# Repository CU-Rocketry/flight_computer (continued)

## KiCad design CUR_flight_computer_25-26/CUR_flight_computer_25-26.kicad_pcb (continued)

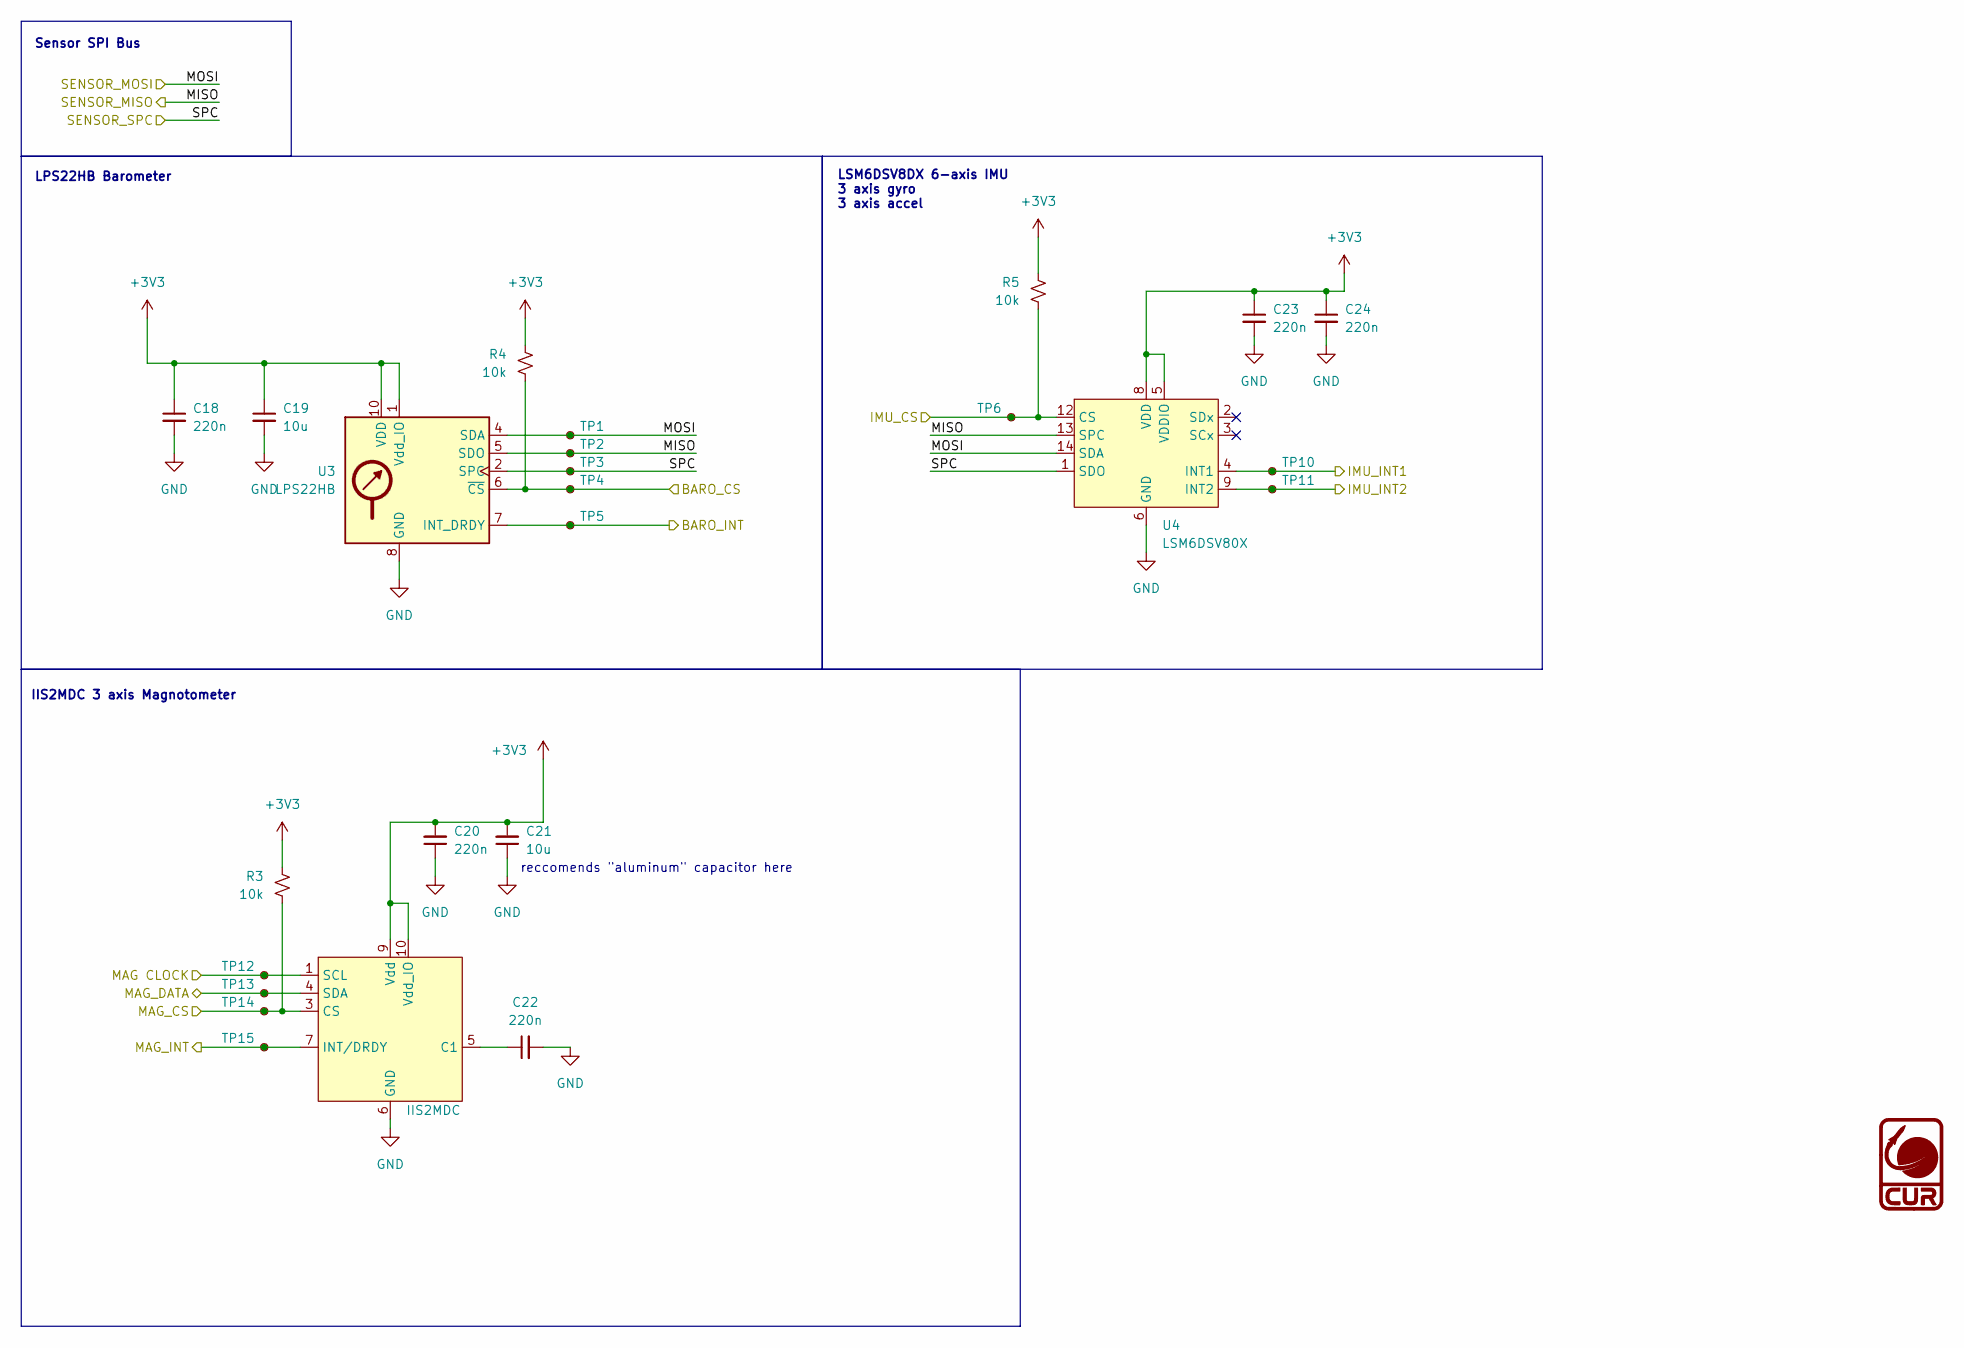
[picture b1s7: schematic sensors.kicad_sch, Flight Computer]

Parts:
C18, C20, C22, C23, C24: 220n; C_0603_1608Metric; MPN 0603B224K250CT
C19, C21: 10u; C_0603_1608Metric; MPN LMK107BBJ106MALT
R3, R4, R5: 10k; R_0603_1608Metric; MPN RC0603FR-0710KL
TP1, TP2, TP3, TP4, TP5, TP6, TP10, TP11, TP12, TP13, TP14, TP15: RCUCTE; TestPoint_Chip_RCUCTE_0603; MPN RCUCTE
U2: IIS2MDC; LGA-12_2X2X0P7_STM; MPN IIS2MDCTR
U3: LPS22HB; ST_HLGA-10_2x2mm_P0.5mm_LayoutBorder3x2y; MPN LPS22HHTR
U4: LSM6DSV80X; LGA-14_3x2.5mm_P0.5mm_LayoutBorder3x4y; MPN LSM6DSV80XTR

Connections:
+3V3: C18.1, C19.1, C20.2, C21.2, C23.1, C24.1, R3.1, R4.1, R5.1, U2.9 (Vdd), U2.10 (Vdd_IO), U3.1 (Vdd_IO), U3.10 (VDD), U4.5 (VDDIO), U4.8 (VDD); also elsewhere on the board
/MCU/BARO_CS: R4.2, TP4.1, U3.6 (~CS); also elsewhere on the board
/MCU/BARO_INT: TP5.1, U3.7 (INT_DRDY); also elsewhere on the board
/MCU/IMU_CS: R5.2, TP6.1, U4.12 (CS); also elsewhere on the board
/MCU/IMU_INT1: TP10.1, U4.4 (INT1); also elsewhere on the board
/MCU/IMU_INT2: TP11.1, U4.9 (INT2); also elsewhere on the board
/MCU/MAG CLOCK: TP12.1, U2.1 (SCL); also elsewhere on the board
/MCU/MAG_CS: R3.2, TP14.1, U2.3 (CS); also elsewhere on the board
/MCU/MAG_DATA: TP13.1, U2.4 (SDA); also elsewhere on the board
/MCU/MAG_INT: TP15.1, U2.7 (INT/DRDY); also elsewhere on the board
/Sensors/MISO: TP2.1, U3.5 (SDO), U4.13 (SPC); also elsewhere on the board
/Sensors/MOSI: TP1.1, U3.4 (SDA), U4.14 (SDA); also elsewhere on the board
/Sensors/SPC: TP3.1, U3.2 (SPC), U4.1 (SDO); also elsewhere on the board
GND: C18.2, C19.2, C20.1, C21.1, C22.2, C23.2, C24.2, U2.6 (GND), U2.8 (GND), U3.3 (GND), U3.8 (GND), U3.9 (GND), U4.6 (GND), U4.7 (GND); also elsewhere on the board
unnamed: C22.1, U2.5 (C1)

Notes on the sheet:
LSM6DSV8DX 6-axis IMU 3 axis gyro 3 axis accel
IIS2MDC 3 axis Magnotometer
reccomends "aluminum" capacitor here
Sensor SPI Bus
LPS22HB Barometer

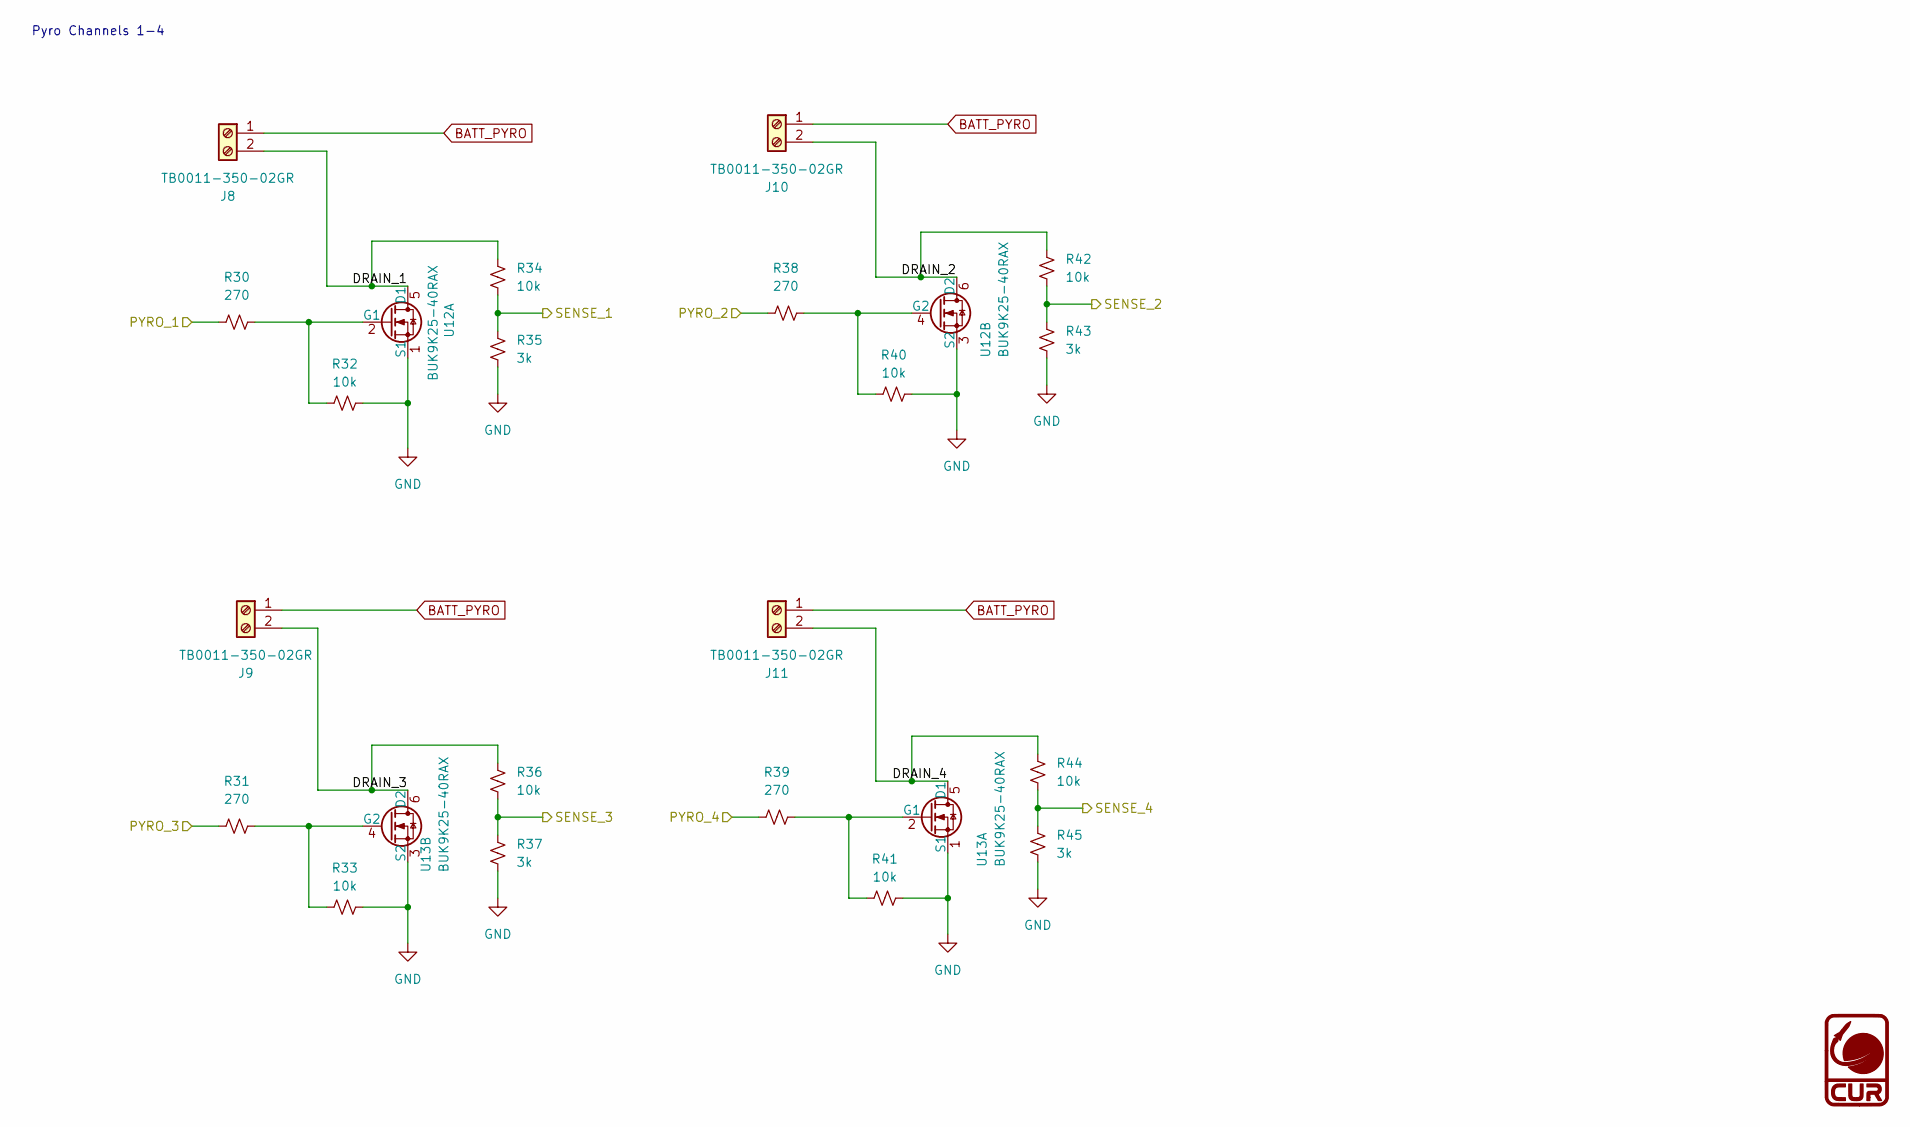
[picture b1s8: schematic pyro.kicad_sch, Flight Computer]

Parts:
J8, J9, J10, J11: TB0011-350-02GR; SAMESKY_TB0011-350-02GR; MPN TB0011-350-02GR
R30, R31, R38, R39: 270; R_0603_1608Metric; MPN RC0603JR-07270RL
R32, R33, R34, R36, R40, R41, R42, R44: 10k; R_0603_1608Metric; MPN RC0603FR-0710KL
R35, R37, R43, R45: 3k; R_0603_1608Metric; MPN RC0603FR-073KL
U12, U13: BUK9K25-40RAX; BUK9K2540RAX; MPN BUK9K25-40RAX

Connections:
/MCU/PYRO_1: R30.1; also elsewhere on the board
/MCU/PYRO_2: R38.1; also elsewhere on the board
/MCU/PYRO_3: R31.1; also elsewhere on the board
/MCU/PYRO_4: R39.1; also elsewhere on the board
/MCU/SENSE_1: R34.2, R35.1; also elsewhere on the board
/MCU/SENSE_2: R42.2, R43.1; also elsewhere on the board
/MCU/SENSE_3: R36.2, R37.1; also elsewhere on the board
/MCU/SENSE_4: R44.2, R45.1; also elsewhere on the board
/Pyro/DRAIN_1: J8.2, R34.1, U12.5 (D1)
/Pyro/DRAIN_2: J10.2, R42.1, U12.6 (D2)
/Pyro/DRAIN_3: J9.2, R36.1, U13.6 (D2)
/Pyro/DRAIN_4: J11.2, R44.1, U13.5 (D1)
BATT_PYRO: J8.1, J9.1, J10.1, J11.1; also elsewhere on the board
GND: R32.2, R33.2, R35.2, R37.2, R40.2, R41.2, R43.2, R45.2, U12.1 (S1), U12.3 (S2), U13.1 (S1), U13.3 (S2); also elsewhere on the board
unnamed: R30.2, R32.1, U12.2 (G1)
unnamed: R38.2, R40.1, U12.4 (G2)
unnamed: R39.2, R41.1, U13.2 (G1)
unnamed: R31.2, R33.1, U13.4 (G2)

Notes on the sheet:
Pyro Channels 1-4

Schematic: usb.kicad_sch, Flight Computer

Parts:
J12: UJ20-C-H-G-SMT-5-P16-TR; SAMESKY_UJ20-C-H-G-SMT-5-P16-TR; MPN UJ20-C-H-G-SMT-5-P16-TR
R46, R47: 5.1k; R_0603_1608Metric; MPN RC0603FR-075K1L
U14: USBLC6-2SC6; SOT-23-6; MPN USBLC6-2SC6

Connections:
/MCU/USB_D+: U14.4 (I/O2); also elsewhere on the board
/MCU/USB_D-: U14.6 (I/O1); also elsewhere on the board
GND: J12.A1 (GND), J12.A12 (GND), J12.B1 (GND), J12.B12 (GND), J12.S1 (SHIELD), R46.2, R47.2, U14.2 (GND); also elsewhere on the board
unnamed: J12.A5 (CC1), R46.1
unnamed: J12.B5 (CC2), R47.1
unnamed: J12.A6 (D+), J12.B6 (D+), U14.3 (I/O2)
unnamed: J12.A7 (D-), J12.B7 (D-), U14.1 (I/O1)
VBUS: J12.A4 (VBUS), J12.A9 (VBUS), J12.B4 (VBUS), J12.B9 (VBUS), U14.5 (VBUS); also elsewhere on the board

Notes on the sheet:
ESD Protection Place near connector
USB

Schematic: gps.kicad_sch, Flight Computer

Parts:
C33: 2.2u; C_0603_1608Metric; MPN CL10B225KP8NNNC
R28, R29: 0; R_0603_1608Metric; MPN RC0603JR-070RL
TP32, TP33, TP34, TP35, TP36, TP38, TP39: RCUCTE; TestPoint_Chip_RCUCTE_0603; MPN RCUCTE
U11: SAM-M8Q; ublox_SAM-M8Q; MPN SAM-M8Q-0

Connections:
+3V3: C33.1, U11.2 (VCC_IO), U11.3 (V_BCKP), U11.17 (VCC); also elsewhere on the board
/GPS/GPS_EXINT: TP32.1, U11.19 (EXTINT); also elsewhere on the board
/GPS/GPS_RX: R29.2; also elsewhere on the board
/GPS/GPS_TP: TP33.1, U11.7 (TIMEPULSE); also elsewhere on the board
/GPS/GPS_TX: R28.2; also elsewhere on the board
/GPS/~GPS_RESET: TP34.1, U11.18 (~RESET); also elsewhere on the board
/LCD_SCL: TP39.1, U11.12 (SCL); also elsewhere on the board
/LCD_SDA: TP38.1, U11.9 (SDA); also elsewhere on the board
GND: C33.2, U11.1 (GND), U11.4 (GND), U11.5 (GND), U11.6 (GND), U11.10 (GND), U11.11 (GND), U11.15 (GND), U11.16 (GND), U11.20 (GND); also elsewhere on the board
unnamed: R28.1, TP35.1, U11.14 (RXD)
unnamed: R29.1, TP36.1, U11.13 (TXD)

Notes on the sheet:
UBlox SAM-MQ8 GPS
external reprogramming header
Funky ass RX/TX switcher
reset has internal pull up resistor
connect safe boot to solderable pad

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
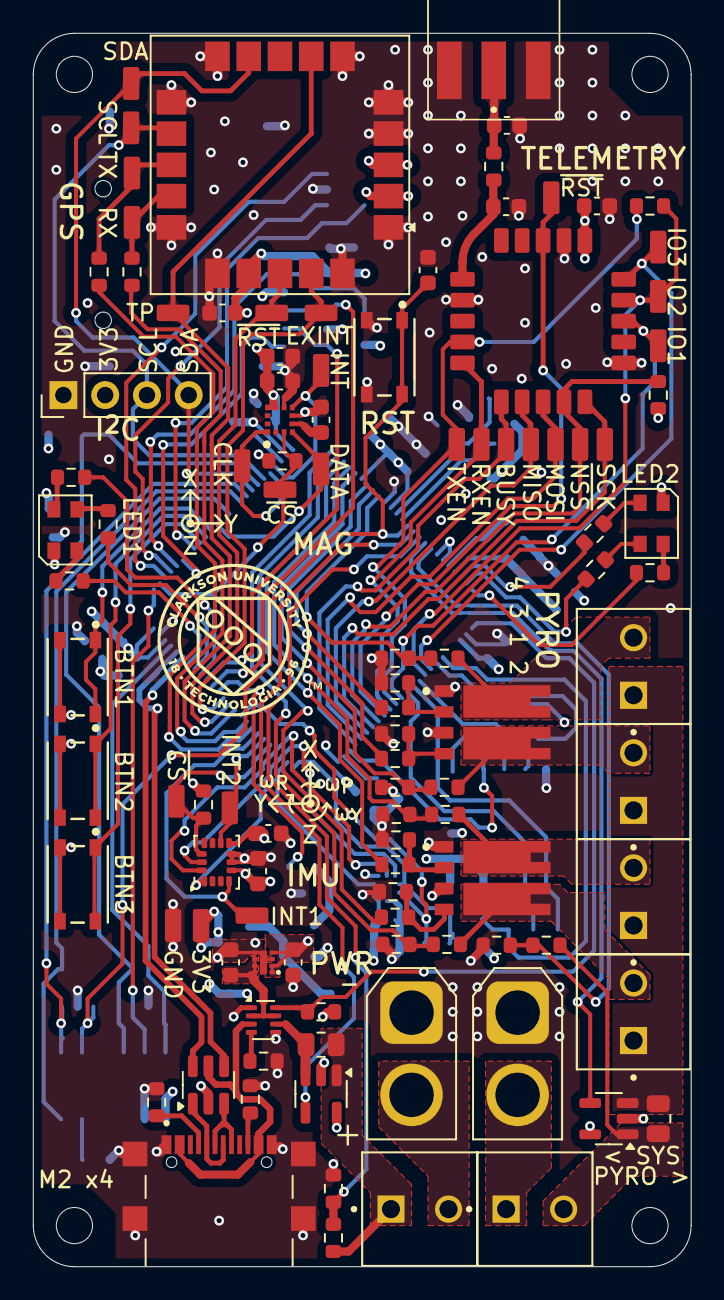
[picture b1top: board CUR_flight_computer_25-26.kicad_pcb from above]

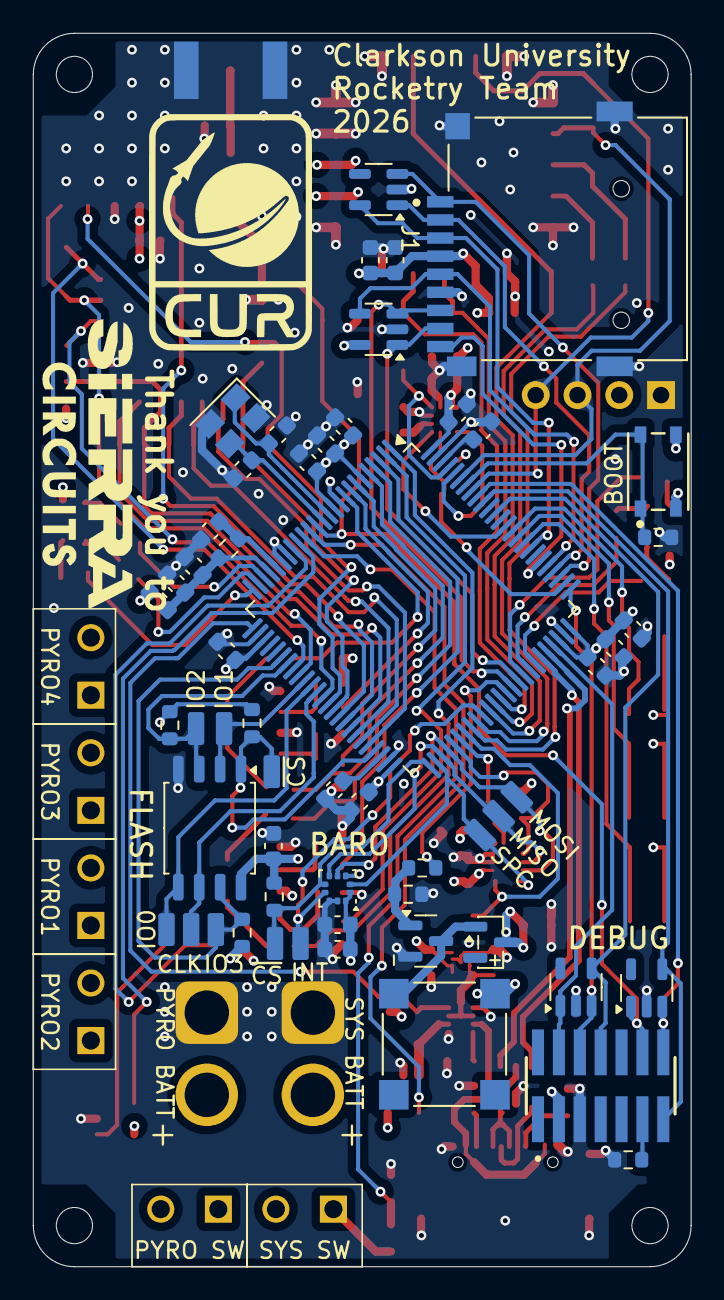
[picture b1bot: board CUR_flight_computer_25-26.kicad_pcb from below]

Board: 4 copper layers, 40.0 x 75.0 mm, 166 parts (56 on the bottom side), 118 nets.

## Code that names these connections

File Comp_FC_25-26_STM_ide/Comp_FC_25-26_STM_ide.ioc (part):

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Mcu.Name=STM32H523VETx
Mcu.Package=LQFP100
Mcu.UserName=STM32H523VETx
PA0.GPIOParameters=GPIO_Label,PinAttribute
PA0.GPIO_Label=LED_2_R
PA0.PinAttribute=Free
PA0.Signal=S_TIM2_CH1
PA1.GPIOParameters=GPIO_Label,PinAttribute
PA1.GPIO_Label=LED_2_G
PA1.PinAttribute=Free
PA1.Signal=S_TIM2_CH2
PA10.GPIOParameters=GPIO_Label,PinAttribute
PA10.GPIO_Label=LED_1_R
PA10.PinAttribute=Free
PA10.Signal=S_TIM1_CH3
PA11.Mode=Device
PA11.Signal=USB_DM
PA12.Mode=Device
PA12.Signal=USB_DP
PA13(JTMS/SWDIO).Mode=Trace_Asynchronous_SW
PA13(JTMS/SWDIO).Signal=DEBUG_JTMS-SWDIO
PA14(JTCK/SWCLK).Mode=Trace_Asynchronous_SW
PA14(JTCK/SWCLK).Signal=DEBUG_JTCK-SWCLK
PA15(JTDI).GPIOParameters=PinState,GPIO_PuPd,GPIO_Label
PA15(JTDI).GPIO_Label=MAG_CS
PA15(JTDI).GPIO_PuPd=GPIO_PULLUP
PA15(JTDI).PinState=GPIO_PIN_RESET
PA15(JTDI).Signal=GPIO_Output
PA2.GPIOParameters=GPIO_Label,PinAttribute
PA2.GPIO_Label=LED_2_B
PA2.PinAttribute=Free
PA2.Signal=S_TIM2_CH3
PA3.GPIOParameters=GPIO_Label,PinAttribute
PA3.GPIO_Label=LM660_ST
PA3.PinAttribute=Free
PA3.Signal=GPIO_Input
PA6.GPIOParameters=PinAttribute
PA6.Mode=OCTOSPI1_IO[3\:0]
PA6.PinAttribute=Free
PA6.Signal=OCTOSPI1_IO3
PA7.GPIOParameters=PinAttribute
PA7.Mode=OCTOSPI1_IO[3\:0]
PA7.PinAttribute=Free
PA7.Signal=OCTOSPI1_IO2
PA8.GPIOParameters=GPIO_Label
PA8.GPIO_Label=LED_1_B
PA8.Signal=S_TIM1_CH1
PA9.GPIOParameters=GPIO_Label,PinAttribute
PA9.GPIO_Label=LED_1_G
PA9.PinAttribute=Free
PA9.Signal=S_TIM1_CH2
PB0.GPIOParameters=PinAttribute
PB0.Mode=OCTOSPI1_IO[3\:0]
PB0.PinAttribute=Free
PB0.Signal=OCTOSPI1_IO1
PB1.GPIOParameters=PinAttribute
PB1.Mode=OCTOSPI1_IO[3\:0]
PB1.PinAttribute=Free
PB1.Signal=OCTOSPI1_IO0
PB10.GPIOParameters=PinAttribute
PB10.Mode=quad_mode
PB10.PinAttribute=Free
PB10.Signal=OCTOSPI1_NCS
PB12.GPIOParameters=GPIO_PuPd,GPIO_Label,PinAttribute
PB12.GPIO_Label=BARO_CS
PB12.GPIO_PuPd=GPIO_PULLUP
PB12.PinAttribute=Free
PB12.Signal=GPIO_Output
PB13.GPIOParameters=PinAttribute
PB13.Mode=Full_Duplex_Master
PB13.PinAttribute=Free
PB13.Signal=SPI2_SCK
PB14.GPIOParameters=PinAttribute
PB14.Mode=Full_Duplex_Master
PB14.PinAttribute=Free
PB14.Signal=SPI2_MISO
PB15.GPIOParameters=PinAttribute
PB15.Mode=Full_Duplex_Master
PB15.PinAttribute=Free
PB15.Signal=SPI2_MOSI
PB2.GPIOParameters=PinAttribute
PB2.Mode=quad_mode
PB2.PinAttribute=Free
PB2.Signal=OCTOSPI1_CLK
PB3(JTDO/TRACESWO).Mode=Trace_Asynchronous_SW
PB3(JTDO/TRACESWO).Signal=DEBUG_JTDO-SWO
PB5.GPIOParameters=PinAttribute
PB5.Mode=Asynchronous
PB5.PinAttribute=Free
PB5.Signal=UART5_RX
PB6.GPIOParameters=PinAttribute
PB6.Mode=Asynchronous
PB6.PinAttribute=Free
PB6.Signal=UART5_TX
PB7.GPIOParameters=PinAttribute
PB7.Mode=I2C
PB7.PinAttribute=Free
PB7.Signal=I2C1_SDA
PB8.GPIOParameters=PinAttribute
PB8.Mode=I2C
PB8.PinAttribute=Free
PB8.Signal=I2C1_SCL
PB9.GPIOParameters=PinAttribute
PB9.Mode=Simplex_Bidirectional_Master
PB9.PinAttribute=Free
PB9.Signal=SPI3_SCK
PC0.GPIOParameters=GPIO_Label,PinAttribute
PC0.GPIO_Label=I_PYRO_SENSE
PC0.PinAttribute=Free
PC0.Signal=ADCx_INP10
PC1.GPIOParameters=GPIO_Label,PinAttribute
PC1.GPIO_Label=BATT_SENSE
PC1.PinAttribute=Free
PC1.Signal=ADCx_INP11
PC10.GPIOParameters=PinAttribute
PC10.PinAttribute=Free
PC10.Signal=SDMMC1_D2
PC11.GPIOParameters=PinAttribute
PC11.PinAttribute=Free
PC11.Signal=SDMMC1_D3
PC12.GPIOParameters=PinAttribute
PC12.PinAttribute=Free
PC12.Signal=SDMMC1_CK
PC13.GPIOParameters=GPIO_Label,PinAttribute
PC13.GPIO_Label=PYRO_3
PC13.PinAttribute=Free
PC13.Signal=GPIO_Input
PC14-OSC32_IN(OSC32_IN).GPIOParameters=GPIO_Label,PinAttribute
PC14-OSC32_IN(OSC32_IN).GPIO_Label=PYRO_4
PC14-OSC32_IN(OSC32_IN).PinAttribute=Free
PC14-OSC32_IN(OSC32_IN).Signal=GPIO_Output
PC15-OSC32_OUT(OSC32_OUT).GPIOParameters=GPIO_Label,PinAttribute
PC15-OSC32_OUT(OSC32_OUT).GPIO_Label=SENSE_4
PC15-OSC32_OUT(OSC32_OUT).PinAttribute=Free
PC15-OSC32_OUT(OSC32_OUT).Signal=GPIO_Input
PC2.GPIOParameters=GPIO_Label,PinAttribute
PC2.GPIO_Label=I_SENSE
PC2.PinAttribute=Free
PC2.Signal=ADCx_INP12
PC3.GPIOParameters=GPIO_Label,PinAttribute
PC3.GPIO_Label=PYRO_BATT_SENSE
PC3.PinAttribute=Free
PC3.Signal=ADCx_INP13
PC4.GPIOParameters=GPIO_Label,PinAttribute
PC4.GPIO_Label=RF_DIO3
PC4.PinAttribute=Free
PC4.Signal=GPIO_Output
PC5.GPIOParameters=GPIO_Label,PinAttribute
PC5.GPIO_Label=RF_DIO2
PC5.PinAttribute=Free
PC5.Signal=GPIO_Output
PC6.GPIOParameters=GPIO_Label,PinAttribute
PC6.GPIO_Label=GPS_EXTI
PC6.PinAttribute=Free
PC6.Signal=GPXTI6
PC7.GPIOParameters=GPIO_Label,PinAttribute
PC7.GPIO_Label=BUZZER
PC7.PinAttribute=Free
PC7.Signal=S_TIM3_CH2
PC8.GPIOParameters=PinAttribute
PC8.PinAttribute=Free
PC8.Signal=SDMMC1_D0
PC9.GPIOParameters=PinAttribute
PC9.PinAttribute=Free
PC9.Signal=SDMMC1_D1
PD0.GPIOParameters=GPIO_Label,PinAttribute
PD0.GPIO_Label=SD_DET
PD0.PinAttribute=Free
PD0.Signal=GPIO_Input
PD10.GPIOParameters=GPIO_PuPd,GPIO_Label,PinAttribute
PD10.GPIO_Label=IMU_INT1
PD10.GPIO_PuPd=GPIO_PULLDOWN
PD10.PinAttribute=Free
PD10.Signal=GPXTI10
PD11.GPIOParameters=PinAttribute
PD11.Mode=Asynchronous
PD11.PinAttribute=Free
PD11.Signal=UART4_RX
PD12.GPIOParameters=PinAttribute
PD12.Mode=Asynchronous
PD12.PinAttribute=Free
PD12.Signal=UART4_TX
PD13.GPIOParameters=GPIO_PuPd,GPIO_Label,GPIO_ModeDefaultEXTI
PD13.GPIO_Label=BARO_INT
PD13.GPIO_ModeDefaultEXTI=GPIO_MODE_IT_RISING
PD13.GPIO_PuPd=GPIO_NOPULL
PD13.Signal=GPXTI13
PD14.GPIOParameters=GPIO_Label,PinAttribute
PD14.GPIO_Label=GPS_TP
PD14.PinAttribute=Free
PD14.Signal=GPXTI14
PD15.GPIOParameters=GPIO_Label,PinAttribute
PD15.GPIO_Label=GPS_RESET
PD15.PinAttribute=Free
PD15.Signal=GPIO_Output
PD2.GPIOParameters=PinAttribute
PD2.PinAttribute=Free
PD2.Signal=SDMMC1_CMD
PD3.GPIOParameters=GPIO_PuPd,GPIO_Label,PinAttribute
PD3.GPIO_Label=BTN_3
PD3.GPIO_PuPd=GPIO_PULLDOWN
PD3.PinAttribute=Free
PD3.Signal=GPXTI3
PD4.GPIOParameters=GPIO_PuPd,GPIO_Label,PinAttribute
PD4.GPIO_Label=BTN_2
PD4.GPIO_PuPd=GPIO_PULLDOWN
PD4.PinAttribute=Free
PD4.Signal=GPXTI4
PD5.GPIOParameters=GPIO_PuPd,GPIO_Label,PinAttribute
PD5.GPIO_Label=BTN_1
PD5.GPIO_PuPd=GPIO_PULLDOWN
PD5.PinAttribute=Free
PD5.Signal=GPXTI5
PD6.GPIOParameters=PinAttribute
PD6.Mode=Simplex_Bidirectional_Master
PD6.PinAttribute=Free
PD6.Signal=SPI3_MOSI
PD8.GPIOParameters=GPIO_PuPd,GPIO_Label,PinAttribute
PD8.GPIO_Label=IMU_CS
PD8.GPIO_PuPd=GPIO_PULLUP
PD8.PinAttribute=Free
PD8.Signal=GPIO_Output
PD9.GPIOParameters=GPIO_PuPd,GPIO_Label,PinAttribute
PD9.GPIO_Label=IMU_INT2
PD9.GPIO_PuPd=GPIO_PULLDOWN
PD9.PinAttribute=Free
PD9.Signal=GPXTI9
PE0.GPIOParameters=GPIO_Label,PinAttribute
PE0.GPIO_Label=MAG_INT
PE0.PinAttribute=Free
PE0.Signal=GPXTI0
PE10.GPIOParameters=GPIO_Label,PinAttribute
PE10.GPIO_Label=RF_RESET
PE10.PinAttribute=Free
PE10.Signal=GPIO_Output
PE11.GPIOParameters=GPIO_PuPd,GPIO_Label
PE11.GPIO_Label=RF_CS
PE11.GPIO_PuPd=GPIO_PULLUP
PE11.Signal=GPIO_Output
PE12.GPIOParameters=PinAttribute
PE12.Mode=Full_Duplex_Master
PE12.PinAttribute=Free
PE12.Signal=SPI4_SCK
PE13.GPIOParameters=PinAttribute
PE13.Mode=Full_Duplex_Master
PE13.PinAttribute=Free
PE13.Signal=SPI4_MISO
PE14.GPIOParameters=PinAttribute
PE14.Mode=Full_Duplex_Master
PE14.PinAttribute=Free
PE14.Signal=SPI4_MOSI
PE15.GPIOParameters=GPIO_PuPd,GPIO_Label
PE15.GPIO_Label=RF_BUSY
PE15.GPIO_PuPd=GPIO_PULLDOWN
PE15.Signal=GPIO_Input
PE2.GPIOParameters=GPIO_Label,PinAttribute
PE2.GPIO_Label=SENSE_2
PE2.PinAttribute=Free
PE2.Signal=GPIO_Output
PE3.GPIOParameters=GPIO_Label,PinAttribute
PE3.GPIO_Label=PYRO_2
PE3.PinAttribute=Free
PE3.Signal=GPIO_Input
PE4.GPIOParameters=GPIO_Label,PinAttribute
PE4.GPIO_Label=PYRO_1
PE4.PinAttribute=Free
PE4.Signal=GPIO_Output
PE5.GPIOParameters=GPIO_Label,PinAttribute
PE5.GPIO_Label=SENSE_1
PE5.PinAttribute=Free
PE5.Signal=GPIO_Input
PE6.GPIOParameters=GPIO_Label,PinAttribute
PE6.GPIO_Label=SENSE_3
PE6.PinAttribute=Free
PE6.Signal=GPIO_Output
PE7.GPIOParameters=GPIO_Label
PE7.GPIO_Label=RF_DIO1
PE7.Signal=GPXTI7
PE8.GPIOParameters=GPIO_Label,PinAttribute
PE8.GPIO_Label=RF_TXEN
PE8.PinAttribute=Free
PE8.Signal=GPIO_Output
PE9.GPIOParameters=GPIO_Label,PinAttribute
PE9.GPIO_Label=RF_RXEN
PE9.PinAttribute=Free
PE9.Signal=GPIO_Output
PH0-OSC_IN(PH0).Mode=HSE-External-Oscillator
PH0-OSC_IN(PH0).Signal=RCC_OSC_IN
PH1-OSC_OUT(PH1).Mode=HSE-External-Oscillator
PH1-OSC_OUT(PH1).Signal=RCC_OSC_OUT
RCC.HSE_VALUE=16000000
RCC.SYSCLKFreq_VALUE=240000000
RCC.SYSCLKSource=RCC_SYSCLKSOURCE_PLLCLK
board=custom

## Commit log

2025-11-09 Add files via upload
    STM Cube IDE Configuration Files
2025-11-09 Add KiCad Files
2025-11-09 Added Datasheets
    - regulator: buxxsd5wg-e
    - IIS2MDC: Magnometer
    - LSP22HB: Barometer
    - Lsm6dsv16b: IMU
    - RA-01SC: RF Module
    - SAM-M8Q: GPS
2025-11-10 Try this
2025-11-10 Remove lock and autosave
2025-11-10 Add gitignore
2025-11-11 Baro schematic
    Hooked up 4-wire SPI
2025-11-11 Updated MCU
    Slight change to MCU version, changes to stm32h523vet
2025-11-11 Create #auto_saved_files#
2025-11-12 Add kicad-library submodule
2025-11-12 Include ST IMU and BUK9K25 libraries
2025-11-12 Add more items to gitignore
2025-11-17 add kicad modules
    add CUR kicad modules
2025-11-17 added decoupling caps
2025-11-17 added more decoupling
    save cause my computer's gonna die. Added VDD and VBAT decoupling
2025-11-17 switched MCU
    Switched MCU to larger pin version
2025-11-18 Added LDO
2025-11-18 Setup Power
    Setup:
    - current sense
    - voltage sense
    - LDO
    - power switching
    - bat terminals
2025-11-19 Hook up GPS module
2025-11-19 Hook up USB connector
2025-11-19 Use VBUS instead of +5V on usb
2025-11-20 Magnitomer
    Put In Magnitominer
2025-11-20 Added IMU
    - hooked up lsm80
2025-11-20 update gps
2025-12-02 Revert "Magnitomer"
2025-12-03 MCU work
    added decoupling, reset button
    need to figure out vddusb
2025-12-03 Update pyro.kicad_sch
    just added the buk9k25 mosfet
2025-12-03 fixes
    fixed magnitometer
2025-12-03 Implement RF reference design for LoRA module
2025-12-03 PYRO Channel
    Set up PYRO channels 1-4
2025-12-04 Flash
    Stole From Sig
2025-12-04 Update peripherals.kicad_sch
    Updated LED
2025-12-04 BUZZER
    Stole it from Sig
2025-12-04 fixing
2025-12-22 schematic not opening
    trying to fix schematic not opening issue
2025-12-22 shematic not opening
    I think i definitely merged things wrong...
2025-12-22 schematic not opening issue
    yeah there are duplicates of stuff....
2025-12-22 missing ")"
    ugh
2025-12-23 IMU was not added in main
    IMU was not added in main, redrew quickly to commit to main
2025-12-23 updated sensors
    issues with magnitometer syncing... readded
2025-12-23 Revert "updated sensors"
2025-12-23 Revert "IMU was not added in main"
2025-12-23 added mag
    copy pasted magnometer schematic
2025-12-23 Update sensors.kicad_sch
    fixed imu issues by copying imu from correct branch...
2025-12-23 updated pins
    updated all sensor pins
2025-12-23 Fix symbol for buzzer NMOS
    Switched it to match NTR4003N pinout
2025-12-23 updated pins
2025-12-23 Update telemetry.kicad_sch
    added resistor, diode
2025-12-23 Update telemetry.kicad_sch
    weird wire connection issues from merging
2025-12-23 added rf pins
2025-12-23 edited gps
2025-12-23 Revert "edited gps"
2025-12-23 added gps pins
2025-12-23 added dubugging
2025-12-23 updated leds
2025-12-23 added leds
2025-12-23 updated sheet pins
2025-12-23 simple fixes
2025-12-23 added buttons, leds on power
2025-12-23 fixed broken stuff from peripherals 2 commit
2025-12-23 Insert correct symbol for NTR4003N
2026-01-01 added HSE
2026-01-01 updated decoupling
2026-01-01 added boot and reset buttons
2026-01-01 changed boot to spdt
2026-01-02 added feedback resistor
2026-01-02 added SD_card holder
    may need to confirm no pull up resistor required
2026-01-02 organized some stuff
    not a lot of actual work here, just organization. Mostly just stopped because I'm going to eat dinner lol
2026-01-08 started adding communication protocols to cube ide
    - added gps uart
    - added sensor spi
    - added rf spi
    - added flash octospi
    need to:
    - figure out how to add interrupt pins
2026-01-08 slight pin name changes
2026-01-13 more pin hooking up work
    spi
    2- sensors
    3- mag
    4- rf
    uart5- debug
    uart4- gps
2026-01-13 hooked up more pins
    added lcd header as well
2026-01-13 more pin editing
2026-01-19 Add E22-400M30S LoRa module to library
2026-01-19 Add EBYTE LoRa module to Telemetry sheet
2026-01-19 fix caps
2026-01-19 updated power stuff
2026-01-19 led fixes and such
2026-01-20 updated pinout
2026-01-20 updated all needed fixes
2026-01-20 assigned footrpint
    need to double check:
    - HSE
    - Capacitors
    for some unknown reason cur kicad library refuses to work
2026-01-20 assigned usb footprint
2026-01-20 updated a couple footprints
2026-01-20 Revert "updated a couple footprints"
2026-01-20 changed footprints
2026-01-20 updated new coaxial footprint
2026-01-20 Update fp-lib-table
2026-01-21 finished footprints
2026-01-21 started basic layout
2026-01-23 more small organization
2026-01-23 more more organization
2026-01-24 most of layout figured out
    trouble finding room for power
2026-01-25 trying to figure out layout
2026-01-26 semi decent layout
2026-01-26 add new cnc tech smd footprint
2026-01-26 ahhhh my eyes (decent layout)
    put things on both sides
2026-01-27 Update kicad-library
2026-01-27 update surface mount usb footprint
2026-01-27 update footprints
2026-01-27 routing updates
2026-01-27 added new header footprint
2026-01-27 added in debug header to layout
2026-01-27 edited debug header
2026-01-28 add ntr4003 mosfet for buzzer
2026-01-28 added mosfet for buzszer
2026-01-28 added testpoints to schematic
    need to update layout
2026-01-28 added testpoints
2026-01-28 were so back
2026-01-28 were so back again
2026-02-06 updated rf module to ebyte-lora-400MM-22s
    added footprint
    added symbol
    updates schematic
    updated pcb
    need to reroute
2026-02-09 adding rf module
2026-02-12 Update CUR_flight_computer_25-26.kicad_pcb
    gotta find a new smd smaller buzzer, but this is pretty chill
2026-02-12 cahnged buzzer
2026-02-12 updated buzzer
2026-02-14 more layout yay
2026-02-14 updates to tvs diodes
2026-02-18 changed diodes
2026-02-18 started traces...yay
2026-02-19 started routing power and rf section
2026-02-24 routed much of back of the board
    the flash will be awful
    sd card, sensors, rf all routed
2026-02-24 attempted to start routing of gps
    sensors will need to move over, board may need to be expanded to accomodate all of the signal lines on the back of the board
2026-02-24 routed more
    gps and sensors are fully connected
    need to connect last of debug pins to mcu
2026-02-27 routed more of the debug section
2026-02-28 routed all the debug lines!
2026-02-28 flash hooked up!
2026-02-28 started routing power sense lines
2026-03-01 routed hse, updates pyro pins order
2026-03-01 routed pyro and sense lines
    to do: buttons, lcd, buzzer, usb, boot switch, rf antenna
2026-03-04 routing lcd
2026-03-04 trying to route usb
2026-03-05 Enable zone filling
2026-03-05 restart layout, downsize mounting holes
2026-03-05 Remove ESD protection on power
2026-03-05 Begin layout
2026-03-05 Layout power and pyro
2026-03-05 Layout GPS and LoRa
2026-03-05 Improve pyro routing
2026-03-05 Separate STM32 VCAP connection
2026-03-05 Replace SS12 with BAT54
2026-03-05 Layout groups
2026-03-05 Layout baro
2026-03-05 Place battery voltage sense resistors
2026-03-05 Placed LED_1
2026-03-05 Place boot button
2026-03-06 Layout flash and baro
2026-03-06 Finish layout
2026-03-06 Finish routing pyro
2026-03-06 Begin GPS and RF routing
2026-03-07 started routing buttons, debug, and sd card
2026-03-07 fully routed mag, lcd, sd, debug, buttons (right side of board)
2026-03-07 RF and Pyros routed
2026-03-07 routed batt sense and i sense
2026-03-07 Attempting to route gps to mcu
    this is a work in progress, had to undo the sd card lines, currently trying to route the gps
2026-03-07 routed gps and rf
2026-03-08 routing pyro power
2026-03-08 routed sensors
    only things left are some decoupling caps and leds
2026-03-08 Replace LDO
2026-03-08 routed flash
2026-03-09 everything but the led :(
2026-03-09 started labeling stuff
2026-03-09 Fix ground at MCU pin 27
2026-03-09 Add GND via for pins 20-21 on MCU
2026-03-09 Fix anotha gnd
2026-03-09 Anotha one
2026-03-10 working through errors
2026-03-13 updated pcb for ddrc
2026-03-15 Remove JTDI and combine NRST and ~{RESET}
2026-03-15 Move mag CS pin to old JTDI pin
2026-03-16 cleanup under mcu routing
2026-03-16 Begin routing NRST
2026-03-16 Route reset
2026-03-16 Finish fixing mag and debug routing
2026-03-16 Run DRC
2026-03-16 Fix DRC unconnected items
2026-03-16 routed led
2026-03-16 started labeling
    brb
2026-03-16 more labeling
2026-03-16 Labeling
    about done, just needs logos
2026-03-17 done labelling (maybe)
2026-03-17 Fix SMA connector location
2026-03-17 Fix LDO footprint
2026-03-17 Fix minor DRC errors
2026-03-17 Fillet corners
2026-03-17 Move some TP labels
2026-03-17 Fix labels sorry hailey
    I may have missed some
2026-03-17 Add XT30 and SAM-M8Q 3D models
2026-03-17 Fix USB-C 3D model and pins
2026-03-17 Add LED 3D models
2026-03-17 Update MOSFET footprints, add dummy LM66200 3D model
2026-03-17 Update SD card holder and buzzer 3D model
2026-03-17 Update debug header and crystal
2026-03-17 Fix NTR4003N footprint
2026-03-17 Remove NTR4003N from fp-lib-table
2026-03-17 Remove other debug connector for clarity
2026-03-17 Apply MPNs for capacitors and connectors
2026-03-17 Add MPNs for ICs
2026-03-17 Hide MPNs
2026-03-17 Add Sierra fab outputs
2026-03-18 labelled everything
2026-03-18 Cleaned up schematic
2026-03-18 cleaning up and reviewing pcb
2026-03-18 Connect GPS I2C to LCD I2C
2026-03-18 Reroute flash and I2C
2026-03-18 Replace SD card holder, route GPS I2C again
2026-03-18 Adjust vias near SMA connector
2026-03-18 Smooth out flash trace bends
2026-03-18 Space out flash IO lines
2026-03-18 added sd card detect
2026-03-18 Cleanup I_SENSE
2026-03-18 Cleanup IMU routing and add GND via
2026-03-18 Cleanup sensor and debug routing
2026-03-19 Further cleanup debug traces
2026-03-19 Cleanup flash CS
2026-03-19 Cleanup buttons
2026-03-19 Cleanup reset capacitor, RF IO2 to TXEN jumper, and run DRC
2026-03-19 BOM optimize resistors
2026-03-19 BOM optimize TVS diodes on SD card to match debug
2026-03-19 Apply resistor MPNs
2026-03-19 Apply ESDA5V3SC5 MPNs
2026-03-19 BOM optimize 4.7u to 10u caps
2026-03-19 BOM optimize 1u to 2.2u
2026-03-19 BOM optimize 100n to 220n
2026-03-19 Improve mag 220nF capacitor routing
2026-03-19 BOM optimize FB
2026-03-19 Update PCB
2026-03-19 Reorganize fab folder
2026-03-19 Use Sierra reccomended LPS22HH
2026-03-19 Update readme for quote 2
2026-03-19 Redo labels
2026-03-19 Export production files
2026-03-24 Final BOM and gerbers
2026-03-26 Update NCP186 footprint
2026-03-26 Update mag footprint
2026-03-26 Add new fabrication files version
2026-03-27 New revisions to address Sierra footprint paste issues
2026-04-09 updated STMCubeMX
2026-04-09 Generated STM code
2026-04-09 started configuring baro
2026-04-09 generated code
2026-04-09 Idk even know man I'm trying here
2026-04-10 adding stuff for baro
2026-04-12 code
2026-04-13 figured out wtf that function wanted
2026-04-13 pyro testing
2026-04-13 Changes to timer setup
2026-04-13 stuff
2026-04-15 pyro testing and serial config
2026-04-15 updated sensors to include imu and mag
2026-04-22 messing with sensors
2026-04-24 coding, go figure
2026-04-29 update sensors
2026-05-19 trying fixes
2026-05-19 testing
2026-05-25 beginning telemetry code
2026-05-27 writing telemetry tx
2026-05-29 setup most of rf architecture
    ... besides packets and decoding
2026-06-05 more code, who would've guessed
2026-06-07 weird bug fixes
2026-06-09 working on implementing imu
2026-06-09 configure flash
2026-06-10 messing with gpdma settings because of course its not that easy
2026-06-10 starting to implement state estimation
2026-06-13 TRYING TO FIX AND SETTING UP RX
2026-06-13 update for sig
